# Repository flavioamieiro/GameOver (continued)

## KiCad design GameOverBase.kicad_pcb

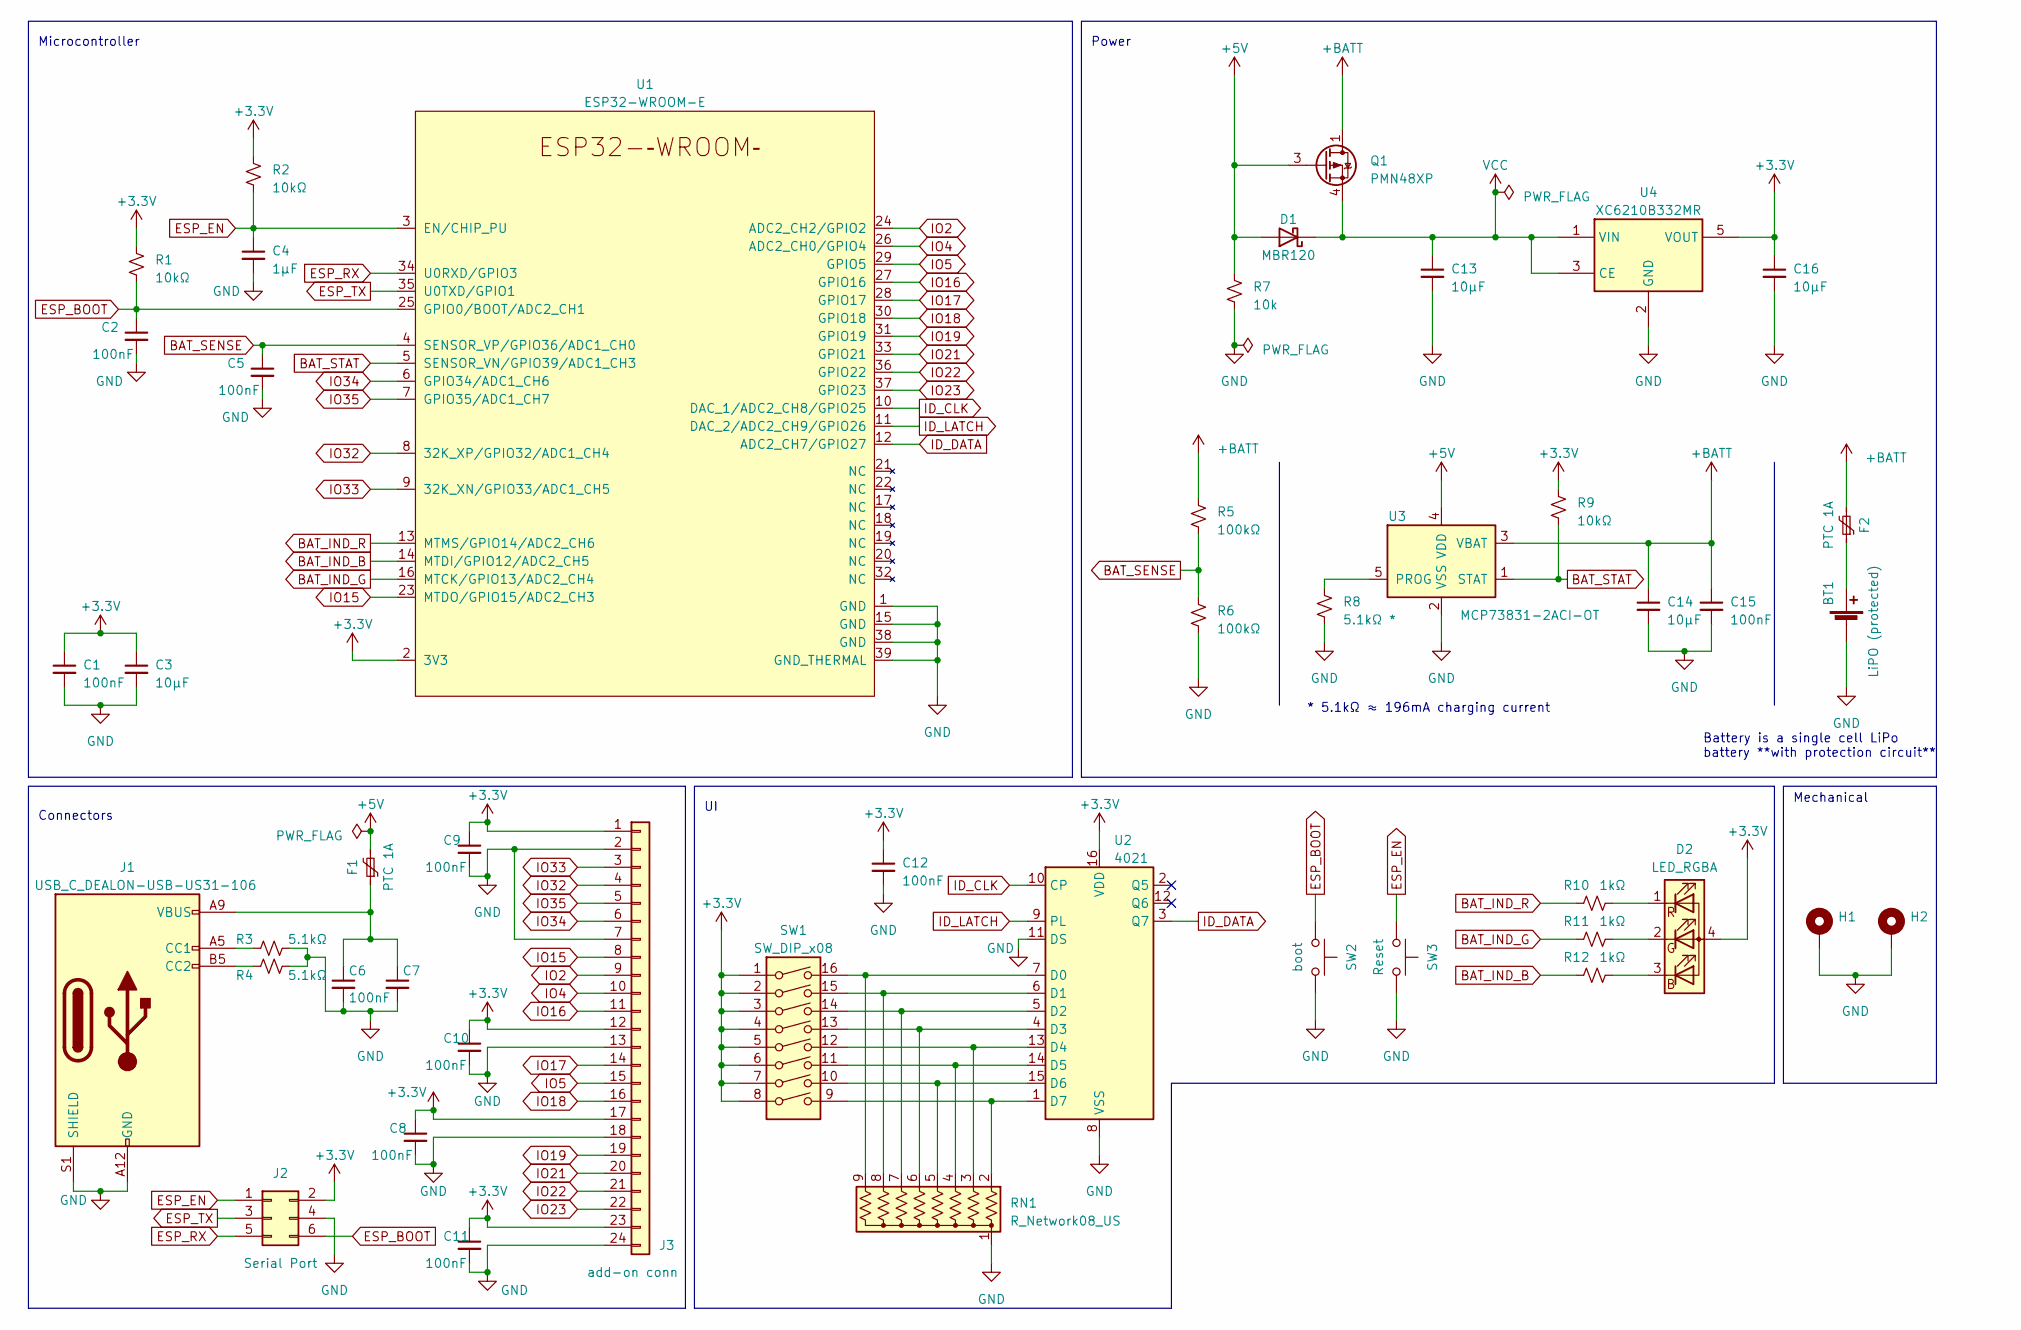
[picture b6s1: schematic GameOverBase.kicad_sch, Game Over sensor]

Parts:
BT1: LiPO (protected); JST_PH_S2B-PH-SM4-TB_1x02-1MP_P2.00mm_Horizontal
C1, C2, C5, C6, C8, C9, C10, C11, C12, C15: 100nF; C_0805_2012Metric_Pad1.18x1.45mm_HandSolder
C3, C13, C14, C16: 10µF; C_0805_2012Metric_Pad1.18x1.45mm_HandSolder
C4: 1µF; C_0805_2012Metric_Pad1.18x1.45mm_HandSolder
C7: C_0805_2012Metric_Pad1.18x1.45mm_HandSolder
D1: MBR120; D_SOD-123
D2: LED_RGBA; Hongzhi_Forest_HS-1204-RGB
F1, F2: PTC 1A; Belfuse_0ZCJ
H1, H2: MountingHole_2.2mm_M2_Pad_Via
J1: USB_C_DEALON-USB-US31-106; DEALON_USB-US31-106
J2: Serial Port; Tag-Connect_TC2030-IDC-FP_2x03_P1.27mm_Vertical
J3: add-on conn; TXGA_FFC05036-24SBD113W5M_1x24_P0.50mm_Horizontal
Q1: PMN48XP; TSOP-6_1.65x3.05mm_P0.95mm
R1, R2, R9: 10kΩ; R_0805_2012Metric_Pad1.20x1.40mm_HandSolder
R3, R4: 5.1kΩ; R_0805_2012Metric_Pad1.20x1.40mm_HandSolder
R5, R6: 100kΩ; R_0805_2012Metric_Pad1.20x1.40mm_HandSolder
R7: 10k; R_0805_2012Metric_Pad1.20x1.40mm_HandSolder
R8: 5.1kΩ *; R_0805_2012Metric_Pad1.20x1.40mm_HandSolder
R10, R11, R12: 1kΩ; R_0805_2012Metric_Pad1.20x1.40mm_HandSolder
RN1: R_Network08_US; R_Array_Convex_5x1206
SW1: SW_DIP_x08; DIP-16_CTS_219-8LPST
SW2: boot; SW_Tactile_SPST_SOFNG_TS-1814
SW3: Reset; SW_Tactile_SPST_SOFNG_TS-1814
U1: ESP32-WROOM-E; ESP32-WROOM-32E
U2: 4021; TSSOP-16_4.4x5mm_P0.65mm
U3: MCP73831-2ACI-OT; SOT-23-5
U4: XC6210B332MR; SOT-23-5

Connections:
+3V3: C1.1, C3.1, C8.1, C9.1, C10.1, C11.1, C12.1, C16.1, D2.4 (A), J2.2, J3.1, J3.12, J3.17, J3.23, R1.1, R2.1, R9.1, SW1.1, SW1.2, SW1.3, SW1.4, SW1.5, SW1.6, SW1.7, SW1.8, U1.2 (3V3), U2.16 (VDD), U4.5 (VOUT)
+5V: D1.2 (A), F1.2, Q1.3 (G), R7.1, U3.4 (VDD)
+BATT: C14.1, C15.1, F2.2, Q1.1 (D), Q1.2 (D), Q1.5 (D), Q1.6 (D), R5.1, U3.3 (VBAT)
BAT_IND_B: R12.1, U1.14 (MTDI/GPIO12/ADC2_CH5)
BAT_IND_G: R11.1, U1.16 (MTCK/GPIO13/ADC2_CH4)
BAT_IND_R: R10.1, U1.13 (MTMS/GPIO14/ADC2_CH6)
BAT_SENSE: C5.1, R5.2, R6.1, U1.4 (SENSOR_VP/GPIO36/ADC1_CH0)
BAT_STAT: R9.2, U1.5 (SENSOR_VN/GPIO39/ADC1_CH3), U3.1 (STAT)
ESP_BOOT: C2.1, J2.6, R1.2, SW2.1, U1.25 (GPIO0/BOOT/ADC2_CH1)
ESP_EN: C4.1, J2.1, R2.2, SW3.1, U1.3 (EN/CHIP_PU)
ESP_RX: J2.5, U1.34 (U0RXD/GPIO3)
ESP_TX: J2.3, U1.35 (U0TXD/GPIO1)
GND: BT1.2 (-), C1.2, C2.2, C3.2, C4.2, C5.2, C6.2, C7.2, C8.2, C9.2, C10.2, C11.2, C12.2, C13.2, C14.2, C15.2, C16.2, H1.1, H2.1, J1.A12 (GND), J1.B12 (GND), J1.S1 (SHIELD), J2.4, J3.2, J3.7, J3.13, J3.18, J3.24, R3.2, R4.2, R6.2, R7.2, R8.2, RN1.1 (common), SW2.2, SW3.2, U1.1 (GND), U1.15 (GND), U1.38 (GND), U1.39 (GND_THERMAL), U2.8 (VSS), U2.11 (DS), U3.2 (VSS), U4.2 (GND)
ID_CLK: U1.10 (DAC_1/ADC2_CH8/GPIO25), U2.10 (CP)
ID_DATA: U1.12 (ADC2_CH7/GPIO27), U2.3 (Q7)
ID_LATCH: U1.11 (DAC_2/ADC2_CH9/GPIO26), U2.9 (PL)
IO2: J3.9, U1.24 (ADC2_CH2/GPIO2)
IO4: J3.10, U1.26 (ADC2_CH0/GPIO4)
IO5: J3.15, U1.29 (GPIO5)
IO15: J3.8, U1.23 (MTDO/GPIO15/ADC2_CH3)
IO16: J3.11, U1.27 (GPIO16)
IO17: J3.14, U1.28 (GPIO17)
IO18: J3.16, U1.30 (GPIO18)
IO19: J3.19, U1.31 (GPIO19)
IO21: J3.20, U1.33 (GPIO21)
IO22: J3.21, U1.36 (GPIO22)
IO23: J3.22, U1.37 (GPIO23)
IO32: J3.4, U1.8 (32K_XP/GPIO32/ADC1_CH4)
IO33: J3.3, U1.9 (32K_XN/GPIO33/ADC1_CH5)
IO34: J3.6, U1.6 (GPIO34/ADC1_CH6)
IO35: J3.5, U1.7 (GPIO35/ADC1_CH7)
unnamed: BT1.1 (+), F2.1
unnamed: D2.3 (BK), R12.2
unnamed: D2.2 (GK), R11.2
unnamed: D2.1 (RK), R10.2
unnamed: J1.A5 (CC1), R3.1
unnamed: J1.B5 (CC2), R4.1
unnamed: C6.1, C7.1, F1.1, J1.A9 (VBUS), J1.B9 (VBUS)
unnamed: RN1.2 (R1), SW1.9, U2.1 (D7)
unnamed: RN1.3 (R2), SW1.12, U2.13 (D4)
unnamed: RN1.4 (R3), SW1.11, U2.14 (D5)
unnamed: RN1.5 (R4), SW1.10, U2.15 (D6)
unnamed: RN1.6 (R5), SW1.13, U2.4 (D3)
unnamed: RN1.7 (R6), SW1.14, U2.5 (D2)
unnamed: RN1.8 (R7), SW1.15, U2.6 (D1)
unnamed: RN1.9 (R8), SW1.16, U2.7 (D0)
unnamed: R8.1, U3.5 (PROG)
VCC: C13.1, D1.1 (K), Q1.4 (S), U4.1 (VIN), U4.3 (CE)

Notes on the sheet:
Microcontroller
Connectors
Battery is a single cell LiPo battery **with protection circuit**
Power
* 5.1kΩ ≈ 196mA charging current
Mechanical

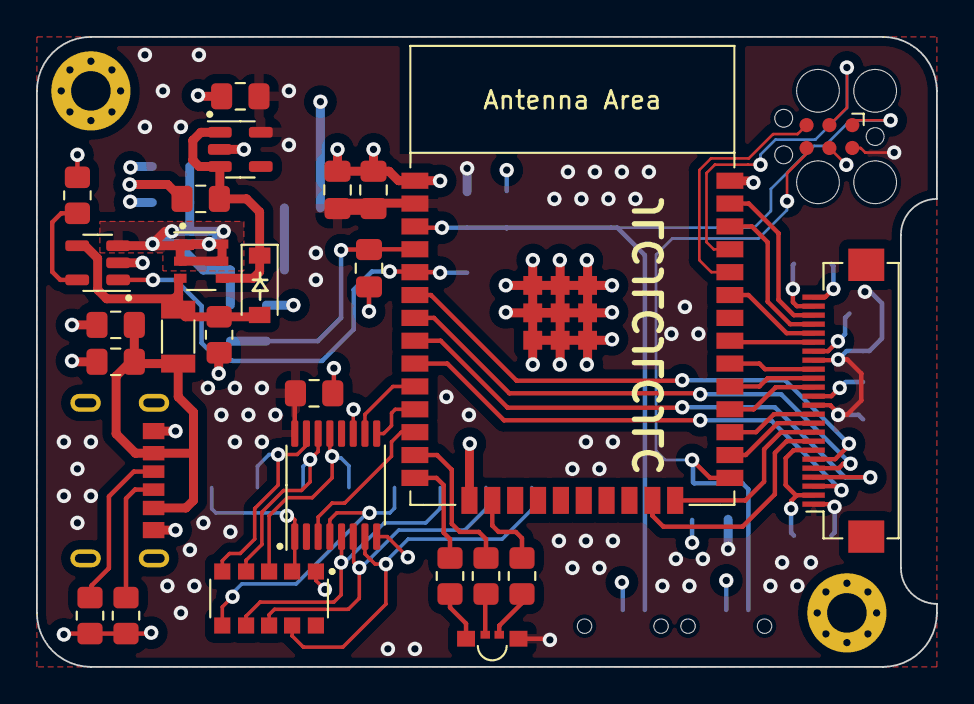
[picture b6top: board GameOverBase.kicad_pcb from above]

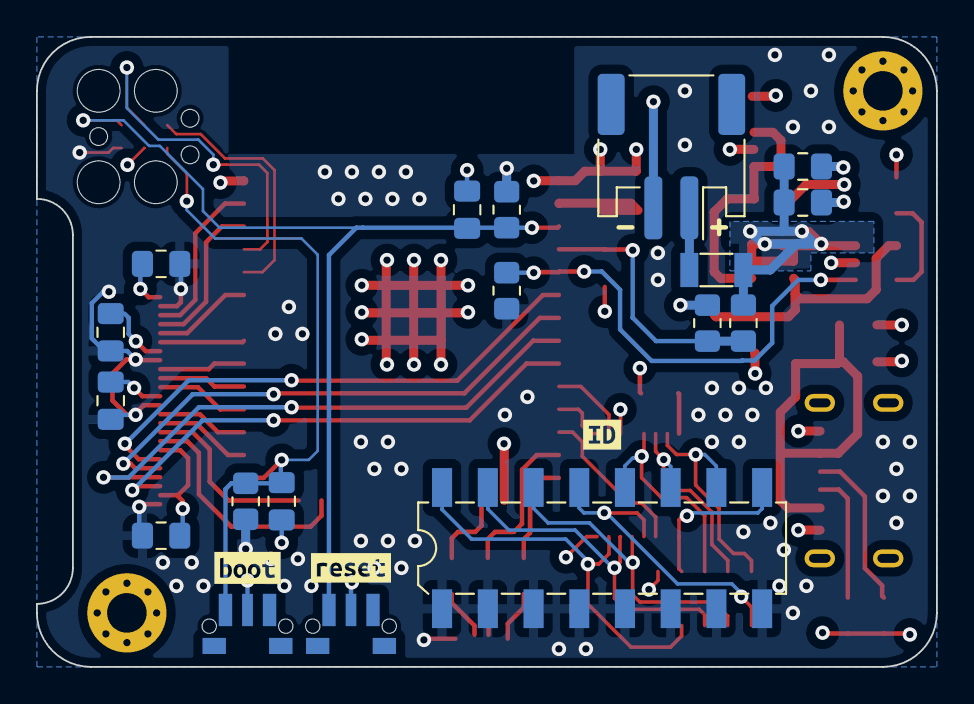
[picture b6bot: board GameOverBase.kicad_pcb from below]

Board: 4 copper layers, 50.0 x 35.0 mm, 50 parts (21 on the bottom side), 48 nets.

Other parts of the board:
kibuzzard-6253FE1B: G***; kibuzzard-6253FE1B
kibuzzard-6253FE4C: G***; kibuzzard-6253FE4C
kibuzzard-6253FE42: G***; kibuzzard-6253FE42

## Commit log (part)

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2022-03-03 Initial draft of a schematic for the sensor
    This uses XC6210B332MR as an LDO (replacing the usual AP2112K-3.3).
    Other ICs that we still don't have a replacement for have placeholders
    for now.
    We decided that the sensors will be programmed through an external
    USB to serial converter to save cost and space.
2022-03-04 Adds battery charging circuit with an MCP73831
    The battery will be 400mA, which means we should use 200mA to charge the
    battery. This would mean a 5kΩ prog resistor. A 5.1kΩ resistor was
    chosen instead to simplify the BOM since we'll already use some of those
    in the USB configuration. This means a charging current of approximately
    196mA.
2022-03-09 Removes on board battery protection circuit
    We decided we will only use battery packs that include their own
    protection mechanism, so we don't need to do it onboard also.
    We still kept the fuse as an extra protection for overcurrent.
2022-03-09 Adds BON055 module symbol
    We will use the Adafruit BON055 breakout board as we couldn't source the
    BNO055 anywhere. This commit includes the schematic symbol but we still
    need to make the footprint to be included in the PCB.
2022-03-10 Fixes pin directions and organizes the schematics a bit better
2022-03-11 Pulls DIP switches down instead of up
    We want the value to be 0 when the switch is open, 1 when it's closed.
2022-03-14 Removes IMU
    This PCB will be the base, on which we will connect other PCBs that add
    functionality to it. The IMU will be on it's own PCB, with it's own LED.
    The keypad will be a third PCB with the buttons and LEDs. The base and
    the add on PCB will be connected by a FFC connector that breaks out the
    the GPIO pins we're not using on the base.
2022-03-14 First draft for the board to board connector
    This is a bad layout, but it breaks out the pins we have left. They will
    be moved around still.
2022-03-14 Moves battery sense pin to ADC1_CH0 (the SENSOR_VP pin)
    This is still in the ADC block 1, so it's not used by wifi, but is
    placed better in the module.
2022-03-14 Rearanges IO pins on connector
    The final position on the connector will probably change during the
    layout to make it easier to route signals, but the pins on the connector
    should be the ones connected now.
2022-03-14 Annotates schematics and runs ERC
2022-03-14 Adds footprint for PTC fuses
    We're using the Belfuse 0ZCJ fuses, but we need to make sure we buy one
    with the same footprint (or change it later).
2022-03-14 Changes RGB led for battery indication to common anode
    This is the kind of LED we bought
2022-03-24 Adds footprint for TXGA FFC05036-24SBD113W5M
    This is the FFC connector we'll use to connect the base to other boards
2022-03-24 Adds footprints for SOFNG TS-1814 tactile switches
2022-03-24 Fixes footprint association for both tactile switches
2022-03-24 Fixes footprint for 4021B
    It actually uses TSSOP16 without thermal pads
2022-03-28 Adds two mouting holes for mechanically mounting the PCB onto the case
    I used M3 screws because they are much easier to find, but if this
    proves too big for the PCB, we can change them to M2.
2022-03-28 Creates specific symbol for the DEALON USB-US31-106 USB-C connector
    This connector has only a subset of the pins necessary for USB-C for
    power only, so we need a specific symbol for it, since the footprint
    will not include all the usual USB-C pins.
2022-03-28 Adds a couple of pre-defined track sizes
2022-03-28 Increases PCB dimensions slightly
    It's now 50mm x 30mm.
2022-03-28 Uses a resistor network for the pull-ups in the ID DIP switch
    This will save a lot of space on the PCB
2022-04-03 Roughly groups together components for the power circuit
2022-04-03 Includes missing components in the power block
    I missed the battery connector, the fuse and the battery sensing voltage
    divider.
2022-04-04 Groups ESP32 circuitry and add-on connector
    To do this, I reorganized the order the GPIO pins are broken out to the
    add-on connector.
    This is still missing the decoupling capacitors on the connector
2022-04-04 Increases board height to 3.5cm
    This increases the overall size quite a bit, but gives us much more
    space, which will be necessary for the DIP switches.
2022-04-04 Brings in DIP switches
    To route this I needed to swap around the pins on the latch and clock
    lines for the 4021 and also the RGB led.
2022-04-04 Adds keepout area for ESP32 antenna
2022-04-04 Flips buttons to the back side of the board
    This side will be highest already because of the DIP switches. It makes
    sense to make an effort for all the tall components to be on the same
    side of the board.
2022-04-07 Brings ESP32 and add-on connector closer together
2022-04-07 Updates kicad files to newer build
2022-04-07 Routes Power section
    This doesn't look like an ideal layout for it, but I had to put the
    battery connector on the other side of the PCB because of it's high
    profile and for lack of space.
2022-04-07 Changes battery connector position
    I need this because I'll change the mechanical hole positions.
2022-04-07 Fixes ERC issues in schematics
2022-04-08 Routes battery status signal to the ESP32
2022-04-08 Moves battery connector further in the board
    This will allow the cable to fit better inside the enclosure
2022-04-08 Routes RGB led
2022-04-08 Adds missing GND connection the te battery sense decoupling cap
2022-04-08 Routes DIP switches for device ID
    This is not a nice route at all, and required changing the pins for the
    resistor network in the schematics to make routing a bit easier.
2022-04-08 Adds generic 3D model to the usb-c connector
    This is *not* the actual connector we'll use. It's added for reference
    only.
2022-04-08 Adds missing connection to battery status pull-up resistor
2022-04-08 HIdes component designators
2022-04-08 Fixes all DRC errors
    This includes removing the 3D models I included for reference. I don't
    want to include them in the actual symbols because they are the wrong
    model.
2022-04-08 Reduces bulk capacitance on usb connector VBUS
    10uF is too much, and could cause an inrush current too big for usb
    specs.
2022-04-11 Tiny reorganization of tracks in the DIP switches
2022-04-11 Adds labels for buttons
2022-04-11 Marks pin 1 of ICs and orientation of diode
2022-04-12 Switches Resistor Network for actual footprint
    We'll use the 746X101 which has a smaller footprint.
2022-04-14 Creates symbol for the connector on add-on boards
2022-04-15 Adds schematics for addon breakout board
2022-04-15 Uses different conn_02x02 symbol that matches footprint
2022-04-15 Positions components on the PCB to match breadboard dimensions
2022-04-15 Adds copper pours for GND and 3v3 on breakout board
2022-04-15 Rotates power pins on the breakout board
    This will make the board sit on the left of the breadboard if the VCC
    power rail is above the ground
2022-04-15 Adds labels to broken out pins
2022-04-15 Adds template for addon board project
2022-04-15 Adds revision number to PCBs
2022-04-15 Adds footprint for Adafruit BNO055 breakout board connector
2022-04-15 Associates connector footprint with adafruit BNO055 breakout symbol
2022-04-15 Connects remaining pins of the BNO055 breakout board
    We don't actually use them, but we had some pins left on the connector,
    so we might as well connect them.
2022-04-15 Associates symbols with footprints on BNO055Sensor
2022-04-15 Adds copper pours for gnd and 3v3 on sensor board
2022-04-15 Fixes DRC errors on sensor board
2022-04-17 Sets gerber output directory
2022-04-17 Adds JLCPCB order number placeholder to breakout board
2022-05-04 Updates PDF schematics
2022-05-04 Adds links to the extra boards on README
2022-05-04 Moves bottom screw hole closer to the edge
    Now that the gap is not as big we can move the screw hole closer to the
    edge. This will not only make the board symmetrical, but also allow the
    buttons to move closer to the edge to make more space for the battery in
    the back.
2022-05-04 Moves boot and reset buttons further to the edge of the board
    This will allow for more space in the center, where we could place the
    battery when in an enclosure.
2022-05-16 Removes DIP switches and supporting circuitry
    We will now use a unique device ID based on the MAC address of the
    ESP32. This will reduce the BOM and make the board easier to assemble.
2022-05-16 Reassociates footprint for the RGB led
2022-05-16 Reroutes pins for the LED
    After fixing the schematic symbol, we needed to reflect the changes in
    the layout.
2022-05-16 Fixes swapped pins on addon connector symbol
2022-05-16 Hides base board connector designator silkscreen
2022-05-16 Adapts breakout board to changes in the addon connector
2022-05-26 Fixes orientation for sensor board
    The idea is to use the base board with the ESP32 facing down, and the
    sensorboard with the sensor facing up. That way the connectors will face
    each other correctly and the sensor will have space above (it wouldn't
    fit between the boards because the battery will already be there).
2022-05-26 Adds schematic symbol and footprint for keypad switches
    We'll use the TL1240GQ1JCLR
2022-05-26 Roughly places components in the keypad PCB
2022-05-27 Swaps switch and led pins for top row
    This will make it easier to route the top buttons.
2022-05-27 Flips buttons on keypad
    The keypad will have the same orientation as the Sensor board (with the
    FFC connector on top). The buttons will be on the same side as the
    connector.
2022-05-27 Adds gameover logo and revision number to keypad PCB
2022-05-27 Moves revision number silkscreen on baseboard
    After adding the new resistor it had no room left where it was.
2022-05-27 Adds logo to BNO055 sensor board schematics
2022-05-27 Fixes logo reference in keypad schematics
2022-05-27 Adds schematic symbol for SSM6L820R mosfet array
2022-05-28 Adds power symbol for switched battery input in library
2022-05-28 Adds datasheet link to SSM6L820R symbol
2022-05-28 Imports power latch components onto PCB
    Also hides the silkscreen references.
2022-05-30 Routes new power latch circuit
2022-05-30 Fixes isolated copper fill warning
2022-05-30 Updates logo in the BreakoutBoard
2022-05-30 Sets output directory for gerber files in keypad
2022-06-04 Adds changes after exporting gerbers from BaseBoard
2022-08-21 Uses fixed LED to indicate charging status instead of the uC
    We're now using a single led to indicate if the battery is currently
    being charged. It will turn off as soon as the battery is fully charged.
2022-08-21 Fixes pin order in the add-connector symbol
    GPIOs 5 and 18 had the order wrong in the add-on connector. This fixes
    the symbol but still doesn't update the other schematics/layouts.
2022-08-21 Rotates the battery connector 90 degrees
    This will make it easier to plug and unplug the battery and to fit the
    entire system in a tight enclosure.
2022-08-21 Reorganizes some traces on the BaseBoard
2022-08-22 Small adjustment to the height of the on/off label
2022-08-22 Refills zones and runs DRC for all boards
2022-08-24 [Enclosure] Moves all common variable and module to a separate file
    The models for the lids will be able to use the same variables.
2022-08-26 Refactors scad files
